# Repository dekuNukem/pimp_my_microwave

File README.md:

# Pimp My Microwave

[More about duckyPad](https://github.com/dekuNukem/duckyPad) | [Official Discord](https://discord.gg/4sJCBx5)

-----

Mechanical keyboards are all the rage these days! People love the satisfying tactile sensation, and some go on great lengths to customise them to their exact liking. 

That begs the question: If we love it *that much*, why stop at just *computer* keyboards?

If you think about it, there are *plenty* of everyday input devices in desperate need of mech-ing up!

For example... a `microwave keypad`??

Yep you heard that right!

Here is the story of how I added a [RGB OLED hot-swap mechanical keypad](https://github.com/dekuNukem/duckyPad) to create the most pimped-up microwave in the entire world!

[Click me](https://www.youtube.com/watch?v=BKcvKsYxbbo) for high-res video with sound!

## Background

A year ago, I picked up a used microwave for £5 at a carboot sale. It was a "`Proline Micro Chef ST44`":

It appears to be from early 2000s, and is pretty unremarkable in every way. But it was cheap and it works, so good enough for me!

## Problem!

That is, until almost exactly a year later. I pressed the usual buttons to heat up my meal, but nothing happened.

After the initial disbelief, my thorough investigation by randomly prodding buttons revealed that the membrane keypad is likely broken. At first a few buttons still worked, but soon  all the buttons stopped responding.

At this point I could have just chucked it and still got my money's worth. But it seemed like a waste just because a cheap plastic keypad failed. Plus I could save a few pounds if I fixed it instead of buying a new one.

So I took it apart and see if there was anything I could do.

## Disassembly

After removing the case, we can see the main circuit board:

* Microcontroller at top-middle

* Buzzer at top-right

* Blue ribbon connector for keypad at middle-left

* Transformer and control relays near the bottom

* Entire board is through-hole, but I guess if it works it works!

Here is the front side:

The board is well marked, and it's interesting to see it uses a [Vacuum Fluorescent Display](https://en.wikipedia.org/wiki/Vacuum_fluorescent_display) (VFD), which was already falling out of favour by the time this was made.

I also noticed this board, and in fact everything inside, was designed by [Daewoo](https://en.wikipedia.org/wiki/Daewoo), a **Korean** conglomerate making everything from cars to, well, this.

Anyway, back to the matter at hand. I thought I could just clean up the ribbon cable contacts and call it a day. Except I didn't notice the contacts were made from carbon(graphite?) instead of the usual metal, and I rubbed some right off:

So if it wasn't broken then, it's definitely broken now. Great job!

## Enter the Matrix (Scanning)

Still, it wasn't the end of the world. The keypad almost certainly uses **`Matrix Scanning`** to interface with the controller.

There is a [detailed introduction of this topic](https://learn.sparkfun.com/tutorials/button-pad-hookup-guide/all) on Sparkfun. But in short, matrix scanning allows us to **read a large number of inputs from limited number of controller pins**. 

For example, there are *more than 100 keys* on our computer keyboard. If we simply connect each key to an input pin, the controller chip will need to have more than 100 pins! It will be bulky, difficult to route, and expensive to produce.

Instead, with a little cleverness in the firmware, we can arrange the buttons in a **grid of columns and rows**, AKA a matrix, like this:

This way, by **scanning a single row and column at a time**, we can determine which key(s) are pressed. Of course there are a lot more technicalities, so [read more here](http://blog.komar.be/how-to-make-a-keyboard-the-matrix/) if you want.

Anyway, in the example above, instead of `4 * 4 = 16` pins, we only need `4 + 4 = 8` pins, a saving of half! And with our computer keyboard, we will only need [around 20 pins](resources/pics/logi.png) instead of more than 100!

Thus, we can see that Matrix Scanning simplifies the pin count and design complexity of input devices.

## Figuring Out the Matrix

Back to our microwave keypad at hand. We can see its ribbon cable comes in two parts, each with 5 pins:

So if my assumptions are correct, it would be a 5x5 matrix with 25 buttons. If you scroll all the way back up, you'll find the keypad has 24 buttons, so it checks out!

Now we know there are 5 columns and 5 rows, it's time to figure out which key is which.

To do that, I desoldered the ribbon cable connector and replaced it with a straight male header:

As a side note, the microcontroller is a [TMP47C412AN](resources/TMP47C412AN.pdf) designed by Toshiba. It is a *4-bit* processor with 4KB of ROM and 128 *Bytes* of RAM. It can also directly drive Vacuum Fluorescent Tubes. So all in all, a very specialised chip for appliances. Very underpowered compared to Arduinos and STM32s. But still, it gets the job done!

I connected some jumper wires:

And labeled the rows and columns with 1-5 and A-E:

I then put the board back, powered on, and touched each pair of wires to see which button it responds as.

It took a while, but eventually I figured out the matrix location of the buttons I need:

|   | A     | B    | C     | D | E     |
|---|-------|------|-------|---|-------|
| 1 | NP_4  | NP_1 |       |   |       |
| 2 | NP_5  | NP_2 |       |   | NP_7  |
| 3 | NP_6  | NP_3 | POWER |   | NP_8  |
| 4 | STOP  |      | TIME  |   | NP_9  |
| 5 | START |      |       |   | NP_10 |

So all in all, 10 numpad keys and 4 control buttons. There are a bunch of other buttons, but I didn't bother since I don't use them anyway.

I quickly whipped up a simple schematic:

With that, I hard-wired some buttons on a perf board as a quick and dirty fix:

It works! At least I'll have hot meals now! And it didn't cost me a dime.

But as you can see, it is very messy with 10 wires coming out of the case, and I'm sure I could do better.

## Pimp It Up!

Around the same time, I was working on [duckyPad](https://github.com/dekuNukem/duckyPad), a 15-key mechanical macropad with **OLED**, **hot-swap**, **RGB**, and sophisticated input automation with [duckyScript](https://github.com/dekuNukem/duckyPad/blob/master/duckyscript_info.md):

[Feel free to check out the project page](https://github.com/dekuNukem/duckyPad) if you're interested!

I called it a `"Do-It-All Macropad"`, so to live up to its name, it was only natural that I get it working on my microwave too!

And if I pull this off, my lowly 20-year-old second-hand broken microwave will transform into the *only one in the entire world* with mechanical switches and RGB lighting! Now that's what I call ... a Korean Custom 😅.

However, it wasn't as easy as it sounds. There are a number of challenges:

* I want to use the existing duckyPad as-is, so no redesigning.

* I want to keep it clean and tidy, so the fewer wires the better.

* It has to be powered by the microwave itself too.

## PMM Board

Right now, there are 10 wires coming out of the case and into my hand-made keypad, very messy.

Ideally, with duckyPad, I want it to use only 3 wires: `Power`, `Ground`, and `Data`. With so few wires, they can be inside a single cable, which would be much more clean and tidy.

However, the microwave controller still expects 10 wires from the keypad matrix. So that means I would need an adapter of some sort. Let's just call it PMM board.

duckyPad would talk to PMM board, which in turn talks to the microwave controller. Something like this:

Not too bad! However, until now we have been using **real switches** with the keypad matrix. But with PMM board, we will need to **control the key matrix electronically** to fool the microwave into thinking we pressed buttons! How do we do it?

## Blast From the Past

It came as a bit of a surprise, but after some digging, it turned out that I solved this *exact* problem 3 years ago! Back then, I was trying to automate inputs of [Nintendo Switch Joycons](https://github.com/dekuNukem/joyAnalog), and they also used matrix scanning for their buttons.

And the answer? [`Analogue Switches!`](https://en.wikipedia.org/wiki/Analogue_switch) You can think of them as regular switches, but instead of pushing them with your fingers, they are controlled electronically.

The chip I used is [ADG714](resources/ADG714_715_new.pdf) from Analog Devices. There are 8 switches in one chip, and they are controlled via simple [SPI protocol](resources/spi.pdf):

I quickly designed the PMM board:

It's a relatively simple board. A STM32F042F6P6 is used, and I broke out all of its pins on headers in case I need them.

Since there are 14 buttons that I want to control, two ADG714s are needed. With SPI, they can be daisy-chained easily.

You can see in the schematic that the analogue switches are wired up in exactly the same way as my shoddy hand-soldered keypad. Except now they can be pressed electronically by the microcontroller.

I had the PCB made, and soldered on all the components:

I did a preliminary testing with continuity beeper, and it seemed to work fine, but we'll only know for sure once it is installed on the real thing.

## Serial-ous Talk

Now the PMM board can control the button matrix, how should duckyPad talk to it?

With only 1 wire for data, I reckoned that a simple one-way serial link should be more than enough.

duckyPad would send a simple serial message at 115200bps every time a key is pressed. The PMM board receives it, and if the format is correct, it would momentarily close the corresponding analog switch, simulating a button press to the microwave.

I added a top-secret [`UARTPRINT`](https://github.com/dekuNukem/duckyPad/blob/d50d58d3c9f0525f0a07fb0c0667dcfdf63f0721/firmware/code/Src/parser.c#L1086) command to the duckyScript parser, and [created a profile](https://github.com/dekuNukem/duckyPad/blob/master/getting_started.md) for my microwave keypad.

They keys on duckyPad is arranged as follows:

## Why So Negative?

It's all coming together! Which brings us to the final question: How are we going to power it?

I thought it would be straightforward. There is already a microcontroller on the microwave circuit board, so just tap its power and job done! Turns out, almost but not quite.

Examining the circuit board in detail, it turns out the whole thing runs on *negative voltages*.

We can see it gets -26V from the transformer, steps it down to -12V, then again to -5V. The voltage regulator is a `S7905PIC` fixed-negative-voltage regulator, further confirming this theory.

I'm not sure why it is designed this way, probably has something to do with the AC transformer. Still, it doesn't actually matter that much, as it's just from a different point of reference.

I tapped two power wires from the circuit board to power the PMM board, and in turn, duckyPad:

To reduce confusion, I marked them `0V` and `-5V`.

Usually, we would connect `0V` to GND, and a positive voltage to VCC. But in this case, `0V` is actually at the higher potential. So all I needed to do is connect `-5V` to GND, and `0V` to VCC. The potential difference is still 5V, so everything works.

(Eagle eyed viewers might notice I also covered the buzzer with a sticker. It was so loud!)

## A Duckin' Great Time!

I reinstalled the circuit board, hooked everything up and did a quick test, it works!

You can see the 3 wires going from duckyPad debug header to PMM board, as well as the 10 wires going into the control board where the blue ribbon cable used to be.

I attached the duckyPad to the microwave, chopped off the ends of a cheap USB cable, and used the 4 wires inside to connect everything up through a vent at the bottom.

Voilà! It's done! The first and (probably) only microwave in the entire universe with mechanical switches, OLED, and RGB lighting!

Have you ever experienced the crisp and clicky tactile and audible perfection of Gateron Greens while heating up some frozen junk food at 2am because you're too lazy to cook? Well, *I* have, so there's that!

[Click me](https://www.youtube.com/watch?v=BKcvKsYxbbo) for high-res video with sound!

## I want one too!

If you're interested in duckyPad, you can [learn more about it here](https://github.com/dekuNukem/duckyPad)😅!

And if you want the whole package, unfortunately it would be much more involved.

Each microwave have different keypad matrix layouts, so you'll need to figure them out, and design and build a PMM board yourself. Not a small feat, but at least all the information is here! If you do go down this path, let me know if you have any questions!

Of course there are high voltages and potential of microwave radiation when you take it apart, so be careful!

## Other Stuff

I've done a few other fun projects over the years, feel free to check them out:

[Daytripper: Hide-my-windows Laser Tripwire](https://github.com/dekuNukem/daytripper): Saves the day while you slack off!

[exixe: Miniture Nixie Tube driver module](https://github.com/dekuNukem/exixe): Eliminate the need for vintage chips and multiplexing circuits.

[From Aduino to STM32](https://github.com/dekuNukem/STM32_tutorials): A detailed tutorial to get you started with STM32 development.

[List of all my repos](https://github.com/dekuNukem?tab=repositories)

## Questions or Comments?

Please feel free to [open an issue](https://github.com/dekuNukem/duckypad/issues), ask in the [official duckyPad discord](https://discord.gg/4sJCBx5), DM me on discord `dekuNukem#6998`, or email `dekuNukem`@`gmail`.`com` for inquires.

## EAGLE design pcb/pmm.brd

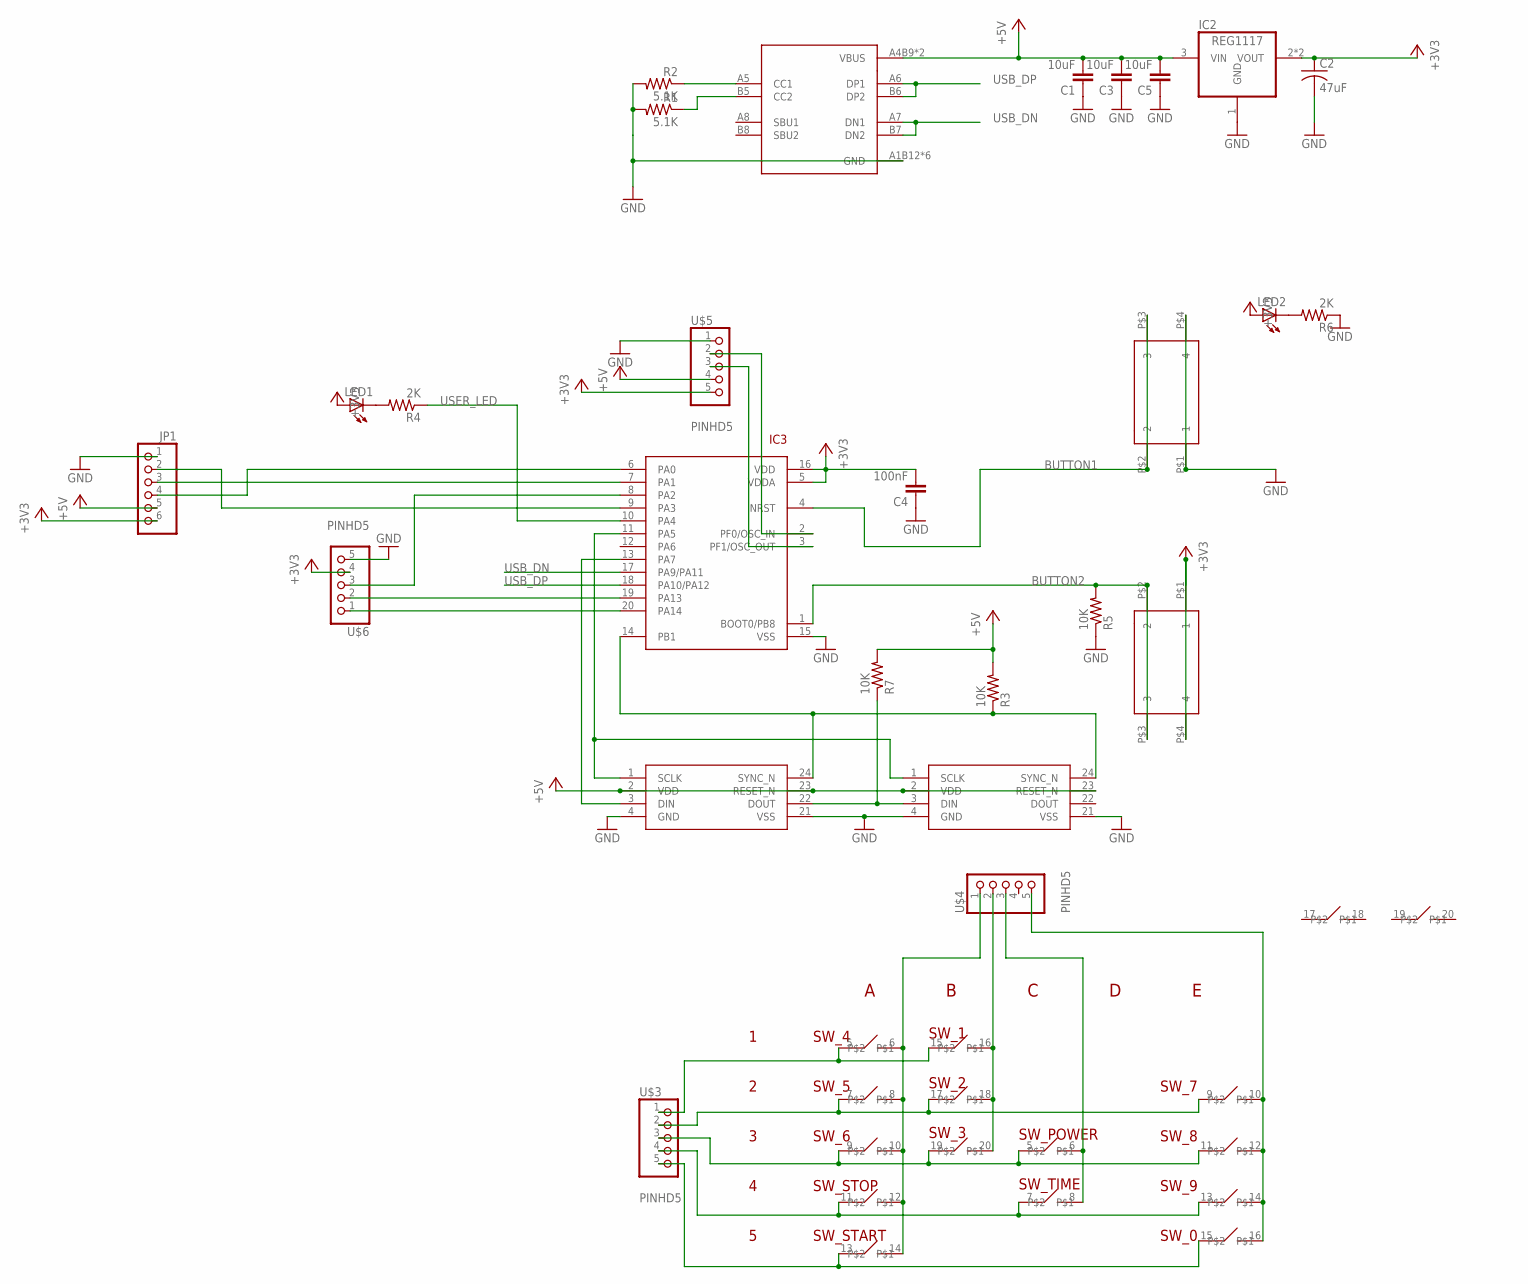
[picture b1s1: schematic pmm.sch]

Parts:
C1, C3, C5: 10uF; 0805@1
C2: 47uF; C1210
C4: 100nF; 0805@1
IC2: REG1117; SOT223
IC3: STM32F042F4; TSSOP20
JP1: PINHD-1X6CB; 1X06-CLEANBIG
LED1, LED2: LEDCHIP-LED0805; CHIP-LED0805
R1, R2: 5.1K; 0805
R3, R5, R7: 10K; 0805
R4, R6: 2K; 0805
SW3, SW4: 324_SW; 342_SWICH_FOOT
U2: USBC_16P; USBC_16P_FOOT
U$1, U$2: ADG714_SEPERATE; TSSOP-24
U$3, U$4, U$5, U$6: PINHD5; 1X05

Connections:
1: U$1.5, U$1.15, U$3.1
2: U$1.7, U$1.17, U$2.9, U$3.2
3: U$1.9, U$1.19, U$2.5, U$2.11, U$3.3
4: U$1.11, U$2.7, U$2.13, U$3.4
5: U$1.13, U$2.15, U$3.5
+3V3: C2.1, C4.2, IC2.2 (VOUT), IC2.4 (VOUT), IC3.5 (VDDA), IC3.16 (VDD), JP1.6, LED1.A, LED2.A, SW4.P$1 (1), SW4.P$4 (4), U$5.5, U$6.4
+5V: C1.2, C3.2, C5.2, IC2.3 (VIN), JP1.5, R3.2, R7.2, U2.A4B9 (VBUS), U2.B4A9 (VBUS), U$1.2 (VDD), U$1.23 (RESET_N), U$2.2 (VDD), U$2.23 (RESET_N), U$5.4
A: U$1.6, U$1.8, U$1.10, U$1.12, U$1.14, U$4.1
B: U$1.16, U$1.18, U$1.20, U$4.2
BUTTON1: IC3.4 (NRST), SW3.P$2 (2), SW3.P$3 (3)
BUTTON2: IC3.1 (BOOT0/PB8), R5.2, SW4.P$2 (2), SW4.P$3 (3)
C: U$2.6, U$2.8, U$4.3
E: U$2.10, U$2.12, U$2.14, U$2.16, U$4.5
GND: C1.1, C2.2, C3.1, C4.1, C5.1, IC2.1 (GND), IC3.15 (VSS), JP1.1, R1.2, R2.2, R5.1, R6.1, SW3.P$1 (1), SW3.P$4 (4), U2.A1B12 (GND), U2.B11A12 (GND), U2.P$13 (GND), U2.P$14 (GND), U2.P$15 (GND), U2.P$16 (GND), U$1.4 (GND), U$1.21 (VSS), U$2.4 (GND), U$2.21 (VSS), U$5.1, U$6.5
unnamed: IC3.11 (PA5), U$1.1 (SCLK), U$2.1 (SCLK)
unnamed: IC3.13 (PA7), U$1.3 (DIN)
unnamed: R7.1, U$1.22 (DOUT), U$2.3 (DIN)
unnamed: IC3.14 (PB1), R3.1, U$1.24 (SYNC_N), U$2.24 (SYNC_N)
unnamed: LED1.C, R4.2
unnamed: IC3.8 (PA2), U$6.3
unnamed: IC3.20 (PA14), U$6.1
unnamed: IC3.19 (PA13), U$6.2
unnamed: IC3.9 (PA3), JP1.2
unnamed: IC3.7 (PA1), JP1.3
unnamed: IC3.6 (PA0), JP1.4
unnamed: IC3.2 (PF0/OSC_IN), U$5.2
unnamed: IC3.3 (PF1/OSC_OUT), U$5.3
unnamed: LED2.C, R6.2
unnamed: R1.1, U2.B5 (CC2)
unnamed: R2.1, U2.A5 (CC1)
USB_DN: IC3.17 (PA9/PA11), U2.A7 (DN1), U2.B7 (DN2)
USB_DP: IC3.18 (PA10/PA12), U2.A6 (DP1), U2.B6 (DP2)
USER_LED: IC3.10 (PA4), R4.1

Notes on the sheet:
1 2 3 4 5
A B C D E
SW_4 SW_5 SW_6 SW_STOP SW_START
SW_1 SW_2 SW_3
SW_POWER SW_TIME
SW_7 SW_8 SW_9 SW_0

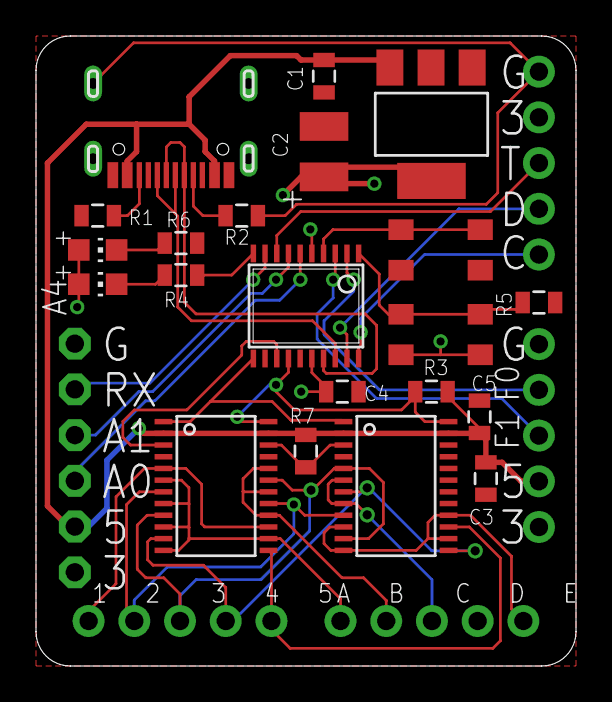
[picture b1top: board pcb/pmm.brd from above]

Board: 2 copper layers, 29.8 x 34.8 mm, 26 parts (0 on the bottom side), 33 nets.

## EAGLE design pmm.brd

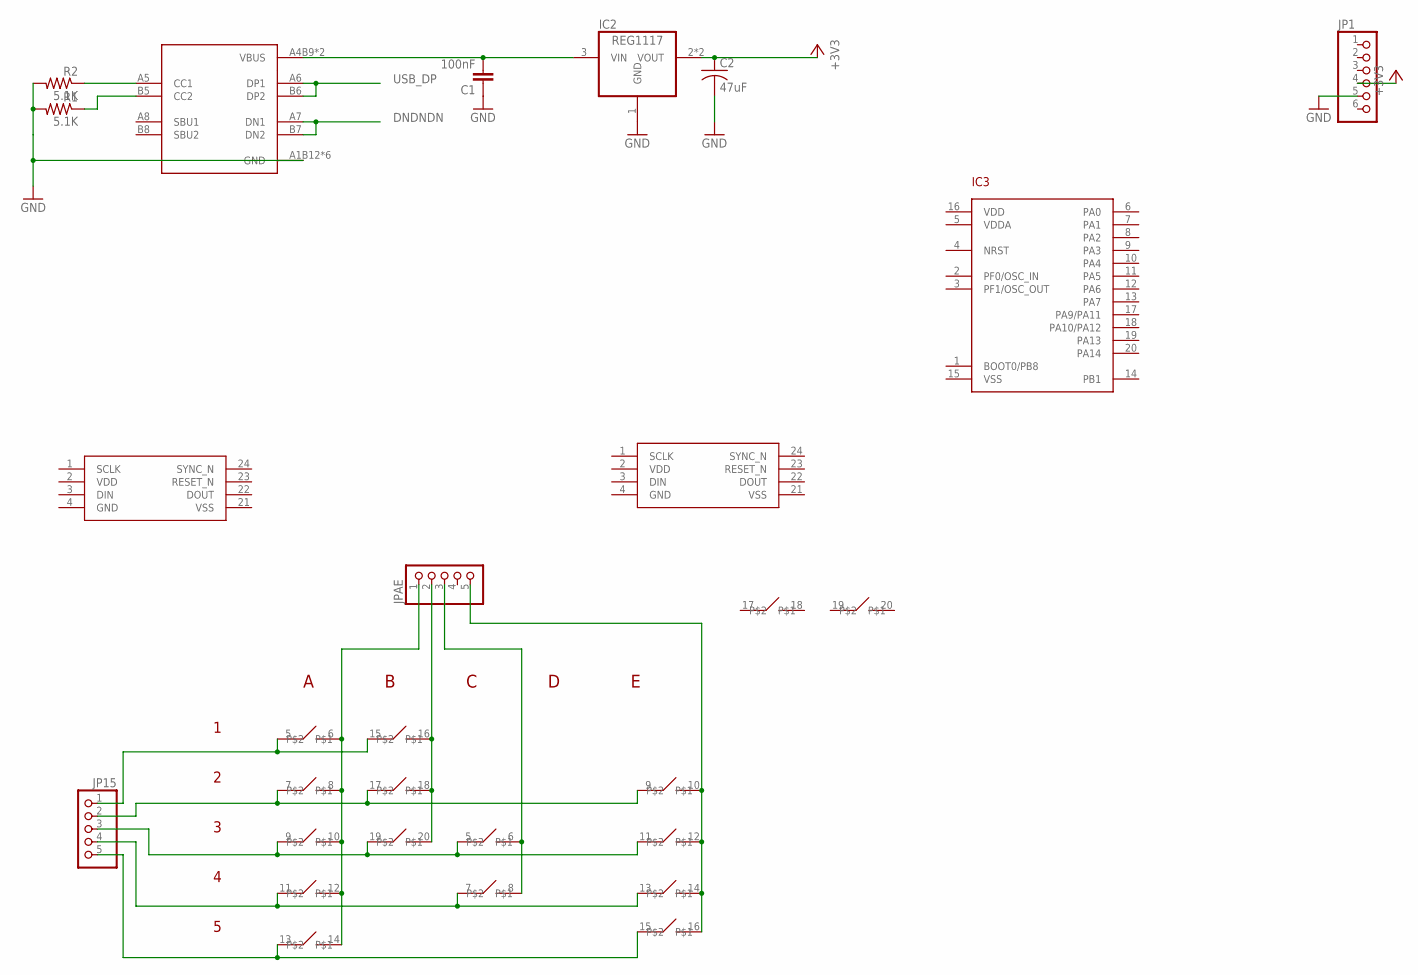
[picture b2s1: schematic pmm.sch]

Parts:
C1: 100nF; 0805@1
C2: 47uF; C1210
IC2: REG1117; SOT223
IC3: STM32F042F4; TSSOP20
JP1: PINHD-1X6; 1X06
JP15: PINHD-1X5; 1X05
JPAE: PINHD-1X5; 1X05
R1, R2: 5.1K; 0805
U2: USBC_16P; USBC_16P_FOOT
U$1, U$2: ADG714_SEPERATE; TSSOP-24

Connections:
1: JP15.1, U$1.5, U$1.15
2: JP15.2, U$1.7, U$1.17, U$2.9
3: JP15.3, U$1.9, U$1.19, U$2.5, U$2.11
4: JP15.4, U$1.11, U$2.7, U$2.13
5: JP15.5, U$1.13, U$2.15
+3V3: C2.1, IC2.2 (VOUT), IC2.4 (VOUT), JP1.4
A: JPAE.1, U$1.6, U$1.8, U$1.10, U$1.12, U$1.14
B: JPAE.2, U$1.16, U$1.18, U$1.20
C: JPAE.3, U$2.6, U$2.8
DNDNDN: U2.A7 (DN1), U2.B7 (DN2)
E: JPAE.5, U$2.10, U$2.12, U$2.14, U$2.16
GND: C1.1, C2.2, IC2.1 (GND), JP1.5, R1.2, R2.2, U2.A1B12 (GND), U2.B11A12 (GND), U2.P$13 (GND), U2.P$14 (GND), U2.P$15 (GND), U2.P$16 (GND)
unnamed: C1.2, IC2.3 (VIN), U2.A4B9 (VBUS), U2.B4A9 (VBUS)
unnamed: R1.1, U2.B5 (CC2)
unnamed: R2.1, U2.A5 (CC1)
USB_DP: U2.A6 (DP1), U2.B6 (DP2)

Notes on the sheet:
1 2 3 4 5
A B C D E

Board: 2 copper layers, 12 parts (0 on the bottom side), 16 nets, no tracks yet.

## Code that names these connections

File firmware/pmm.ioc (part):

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Mcu.Name=STM32F042F6Px
Mcu.Package=TSSOP20
Mcu.UserName=STM32F042F6Px
PA13.Mode=Serial_Wire
PA13.Signal=SYS_SWDIO
PA14.Mode=Serial_Wire
PA14.Signal=SYS_SWCLK
PA2.Mode=Asynchronous
PA2.Signal=USART2_TX
PA3.Mode=Asynchronous
PA3.Signal=USART2_RX
PA4.GPIOParameters=PinState,GPIO_Label
PA4.GPIO_Label=USER_LED
PA4.PinState=GPIO_PIN_SET
PA4.Signal=GPIO_Output
PA5.Mode=Full_Duplex_Master
PA5.Signal=SPI1_SCK
PA6.Mode=Full_Duplex_Master
PA6.Signal=SPI1_MISO
PA7.Mode=Full_Duplex_Master
PA7.Signal=SPI1_MOSI
PB1.GPIOParameters=PinState,GPIO_Label,GPIO_ModeDefaultOutputPP
PB1.GPIO_Label=SPI1_CS
PB1.GPIO_ModeDefaultOutputPP=GPIO_MODE_OUTPUT_OD
PB1.PinState=GPIO_PIN_SET
PB1.Signal=GPIO_Output
RCC.SYSCLKFreq_VALUE=48000000
RCC.SYSCLKSource=RCC_SYSCLKSOURCE_HSI48
board=custom

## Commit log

2020-06-28 outline pcb
2020-06-29 pcb done
2020-06-29 minor cleanup
2020-08-16 board hello world
2020-08-16 troubleshooting
2020-08-16 added a required pullup resistor
2020-08-16 board tested working
2020-08-17 2nd prototype
2020-09-13 new board working
2020-09-13 firmware working
2020-09-14 code working
2020-09-15 fixed a UART bug
2020-11-12 finished writeup
2020-11-12 added video link
2020-11-14 fixed a few typos and a shameless plug
2020-11-14 more typo fix
2020-11-30 post-kickstarter update
2021-04-01 updated bottom layer clearance

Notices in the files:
parts and their libraries:
SparkFun-Passives: Licensing: Creative Commons ShareAlike 4.0 International - https://creativecommons.org/licenses/by-sa/4.0
